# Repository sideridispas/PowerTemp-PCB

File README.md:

# PowerTemp-PCB
Two separated functions of the board, depending on which side is populated:
<ul>
	<li>Side A: PowerSupply
		Takes a DC Voltage (max 30V) as input and gives a fixed stable 5V output. Also has "wrong connection" protection with diodes
		Parts: LM7805CT, 0.33uF & 0.1uF Capacitors, RS1A Diodes, 2-Pin terminals
	</li>
	<li>Side B: Temperature
		Facilitates a DS18B20 sensor and two 3-Pin terminals
	</li>

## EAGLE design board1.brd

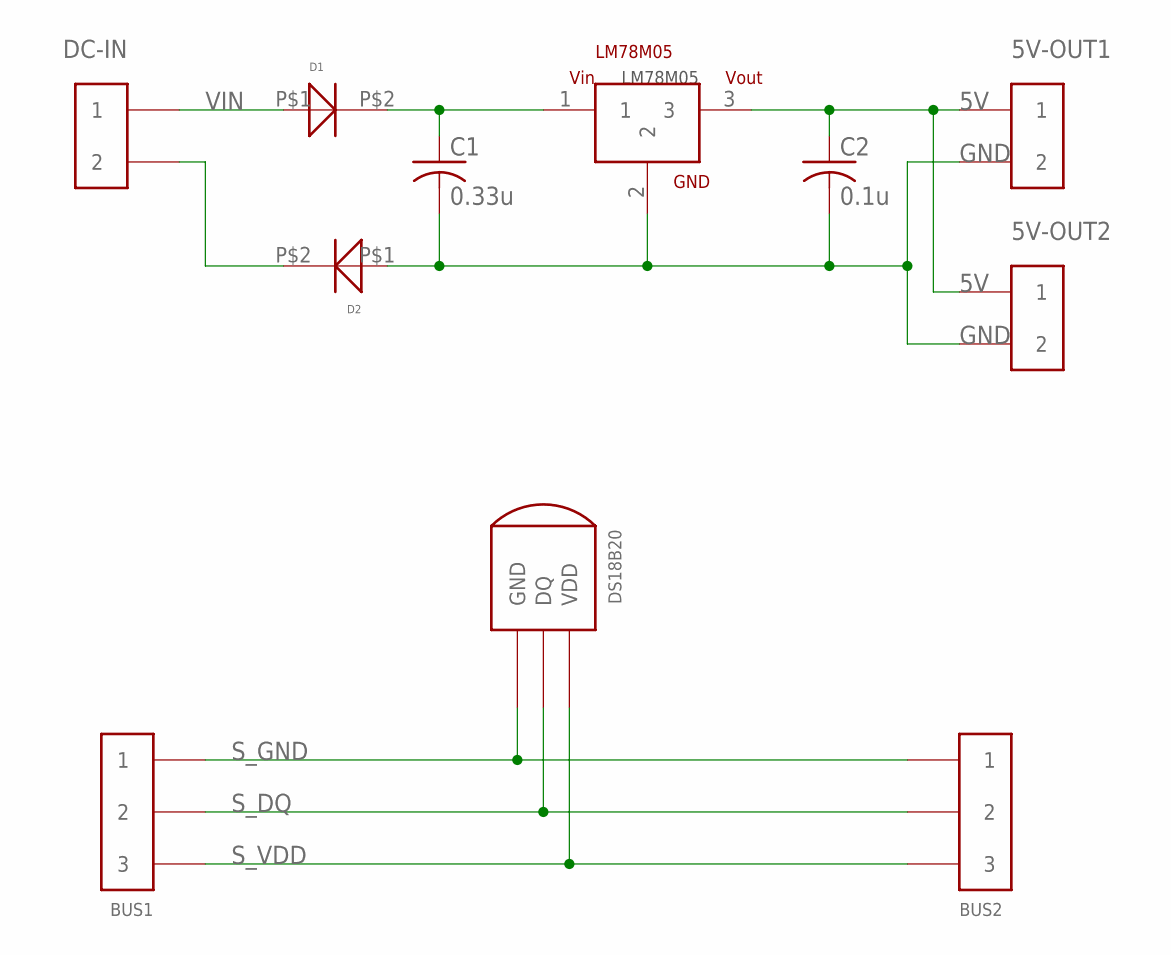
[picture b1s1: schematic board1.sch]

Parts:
5V-OUT1, 5V-OUT2: 2PIN-TERMINAL-5MMPITCH
BUS1, BUS2: AVX-3PIN-SMD-CON
C1: 0.33u; C3216
C2: 0.1u; C3216
D1, D2: DIODE; DIODE_PAC
DC-IN: 2PIN-TERMINAL-5MMPITCH
DS18B20: SMD-3PAD-DS18B20
LM78M05: LM78M05; LM78M05_PAC

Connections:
5V: 5V-OUT1.1, 5V-OUT2.1, C2.1, LM78M05.3
GND: 5V-OUT1.2, 5V-OUT2.2, C1.2, C2.2, D2.P$1 (1), LM78M05.2
unnamed: C1.1, D1.P$2 (2), LM78M05.1
unnamed: D2.P$2 (2), DC-IN.2
S_DQ: BUS1.P$2 (2), BUS2.P$2 (2), DS18B20.P$2 (DQ)
S_GND: BUS1.P$1 (1), BUS2.P$1 (1), DS18B20.P$1 (GND)
S_VDD: BUS1.P$3 (3), BUS2.P$3 (3), DS18B20.P$3 (VDD)
VIN: D1.P$1 (1), DC-IN.1

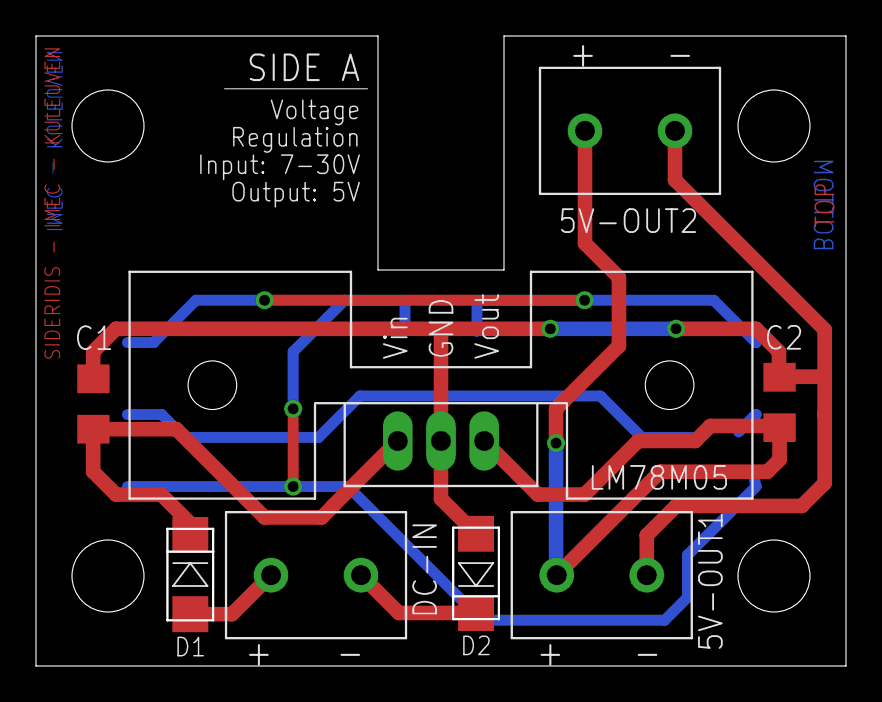
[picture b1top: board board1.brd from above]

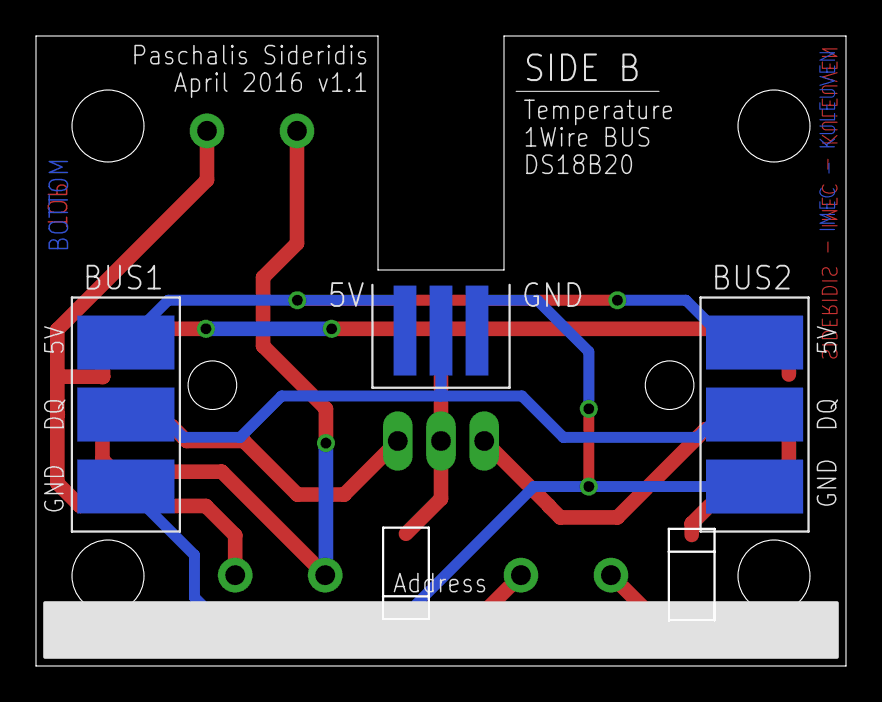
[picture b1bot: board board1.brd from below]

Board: 2 copper layers, 44.9 x 34.9 mm, 11 parts (3 on the bottom side), 8 nets.

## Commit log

2016-04-11 No changes
2016-04-11 Draft version ready, only at Power side
2016-04-13 Final version. Added also vias for soldering external the sensor (maybe we will remove them)
2016-04-13 Removed the vias. Simple design, version v1.0
2016-04-13 Final version v1.0
2016-04-13 Fixed the wrong path for bypass caps. Version v1.1
